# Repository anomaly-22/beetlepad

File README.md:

## Beetlepad
Beetepad is a macropad I created to help me with art. It has 12 keys and an OLED display that displays a idling beetle. It also has a beetle on the case cause I like them

In the future (once I get better at coding) I want to make the keys swappable so there's two buttons above the screen that can be used to switch the key layout
## CAD

Made in Fusion 360. The top and bottom of the case are screwed together. This is also my first time importing DXF files for the holes and beetle on the top and I feel like I'll use it in the future to add things on my team's FTC robot :>

## PCB

Made in Kicad! I had some experience from solder so making the PCB wasn't too bad. 

## BOM

- 1x XIAO RP2040
- 14x Diodes
- 12x Cherry MX Switches
- 1x OLED display
- 12x DSA keycaps
- 4x M3x16mm screws
- 4x M3x5mx4mm heatset inserts
- 1x case

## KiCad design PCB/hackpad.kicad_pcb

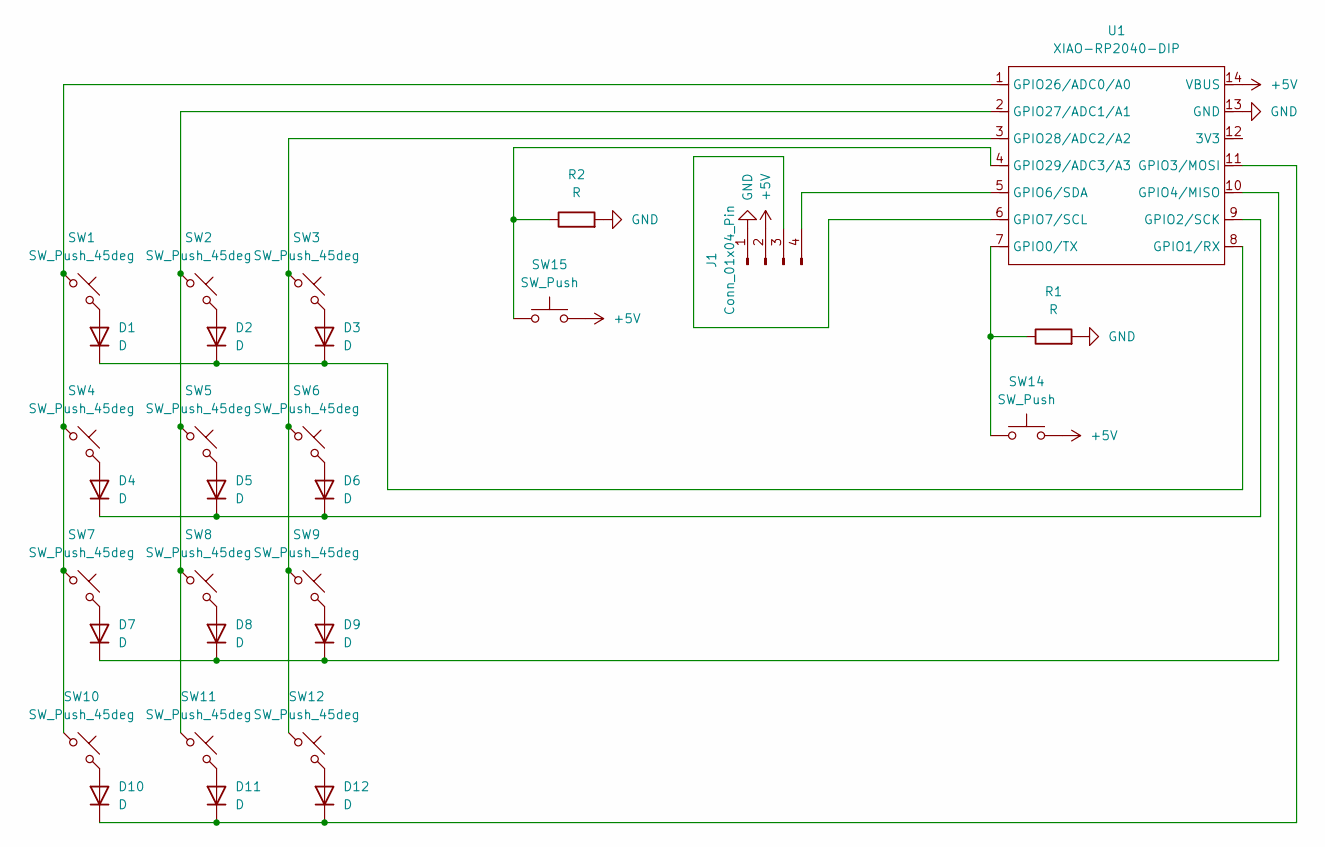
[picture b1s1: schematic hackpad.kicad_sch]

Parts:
D1, D2, D3, D4, D5, D6, D7, D8, D9, D10, D11, D12: D; D_DO-35_SOD27_P7.62mm_Horizontal
J1: Conn_01x04_Pin; MODULE_DM-OLED096-636
R1, R2: R; R_Axial_DIN0207_L6.3mm_D2.5mm_P7.62mm_Horizontal
SW1, SW2, SW3, SW4, SW5, SW6, SW7, SW8, SW9, SW10, SW11, SW12: SW_Push_45deg; SW_Cherry_MX_1.00u_PCB
SW14, SW15: SW_Push; SW_PUSH_6mm
U1: XIAO-RP2040-DIP

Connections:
+5V: J1.2, SW14.2, SW15.2, U1.14 (VBUS)
GND: J1.1, R1.2, R2.2, U1.13 (GND)
unnamed: D1.2 (A), SW1.2
unnamed: D1.1 (K), D2.1 (K), D3.1 (K), U1.8 (GPIO1/RX)
unnamed: D2.2 (A), SW2.2
unnamed: D3.2 (A), SW3.2
unnamed: D4.2 (A), SW4.2
unnamed: D4.1 (K), D5.1 (K), D6.1 (K), U1.9 (GPIO2/SCK)
unnamed: D5.2 (A), SW5.2
unnamed: D6.2 (A), SW6.2
unnamed: D7.2 (A), SW7.2
unnamed: D7.1 (K), D8.1 (K), D9.1 (K), U1.10 (GPIO4/MISO)
unnamed: D8.2 (A), SW8.2
unnamed: D9.2 (A), SW9.2
unnamed: D10.2 (A), SW10.2
unnamed: D10.1 (K), D11.1 (K), D12.1 (K), U1.11 (GPIO3/MOSI)
unnamed: D11.2 (A), SW11.2
unnamed: D12.2 (A), SW12.2
unnamed: J1.3, U1.6 (GPIO7/SCL)
unnamed: J1.4, U1.5 (GPIO6/SDA)
unnamed: R1.1, SW14.1, U1.7 (GPIO0/TX)
unnamed: SW1.1, SW4.1, SW7.1, SW10.1, U1.1 (GPIO26/ADC0/A0)
unnamed: SW2.1, SW5.1, SW8.1, SW11.1, U1.2 (GPIO27/ADC1/A1)
unnamed: SW3.1, SW6.1, SW9.1, SW12.1, U1.3 (GPIO28/ADC2/A2)
unnamed: R2.1, SW15.1, U1.4 (GPIO29/ADC3/A3)

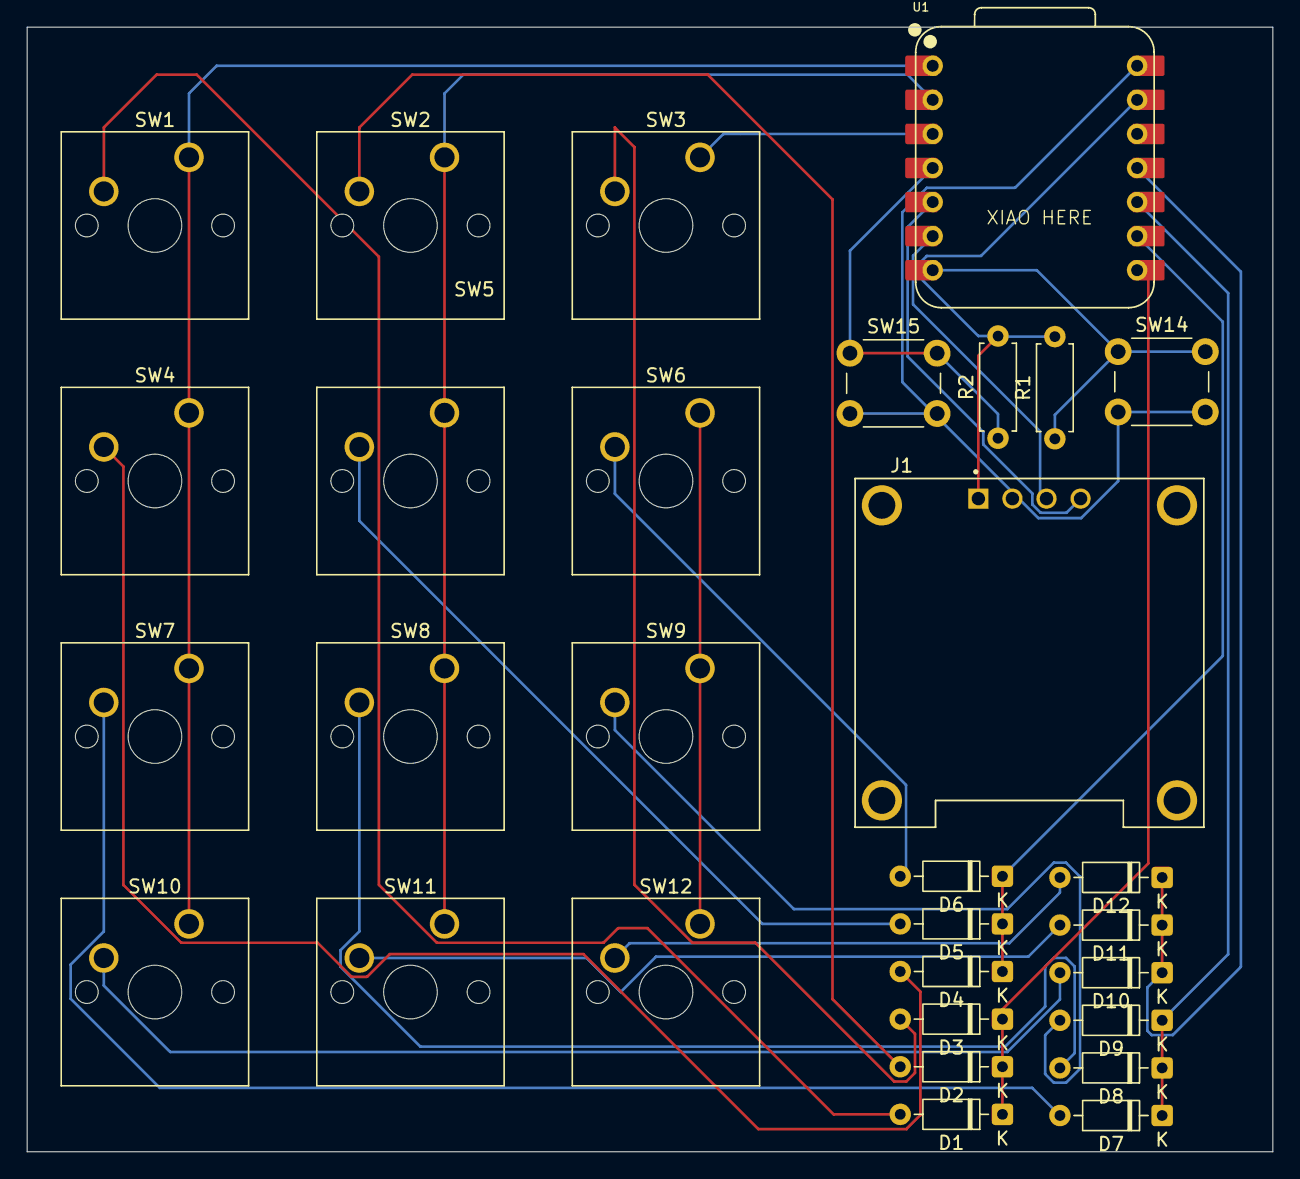
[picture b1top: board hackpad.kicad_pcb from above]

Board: 2 copper layers, 92.9 x 83.8 mm, 30 parts (0 on the bottom side), 25 nets.

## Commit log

2025-06-27 pictures
2025-06-28 fixed pcb picture + label
